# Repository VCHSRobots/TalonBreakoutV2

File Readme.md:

Talon Breakout Board, v2
------------------------

VCHS Robotics, Epic Robotz, Team 4415

December 2018

Epic Robotz has designed a breakout board that works with the Talon SRC manufactured by Cross
the Road Electronics.    This breakout board brings all signals from the data port to connectors
that provide secure connections for wiring to limit switches and encoders.  The breakout board
can be secured directly on the Talon, and the sensor/encoder wires can be directed inline with
the other Talon wiring to improve wire routing on the robot.  The connectors use a strong friction
fit to avoid becoming loose during a match.   This design of the breakout boards (and the
companion encoder PCB) was designed and tested during the Fall of 2018 by Epic Robotz
(Team 4415).  The design is being provided here for other teams to use if they see fit.
The boards where designed with a free version of Autodesk EAGLE pcb design software.  
All the files necessary to produce the breakout boards are included in this repository.

Notes
-----

The PCB is designed to be directly mounted in contact with the Talon.  Since the Talon is made of 
metal, care has been taken to place vias in areas where there is no metal on the Talon. However, 
when purchasing PCB boards with this design, be sure to put solder mask over the vias (which
is normally not done when fabricating prototypes).

It is also important to grind away any excess protrusion of through-hole pins on the solder side where
the connectors are soldered into place.  We have inclucded pictures to show how this is done.  Note
that the PCB traces to the connectors are ALL on the top side, so deep grinding of the bottom where
the connector pins protrude is okay.

For additional electrical insulation between the breakout board and the Talon, we suggest that you
epoxy a "gasket" direcly on the PCB.  All the files to 3D print the gasket are provided here as well
as pictures to show how the glue up is done.

We have included a design for a solder jig that holds the through-hole connectors in place while
soldering.  However, you will need to solder the SMD 2x5 connector with an oven or by hand
using a microscope and solder paste.

Bill of Materials
-----------------

    Talon PCB      --  Procured via a PCB manufacturing company using the gerber files.
                       Each PCB will produce 6 breakout boards, and 6 companion encoder boards.
    
    Gasket        --   1 Gasket per Breakout board.  Obtained via 3D printing.
    
    2x5 Connector --   1 per Breakout board.  Digikey 609-3706-1-ND.  This is an SMD part.
    
    4 pin Header  --   1 per Breakout board. Digikey WM16136-ND. This is a through hole part.
    
    3 pin Header  --   2 per Breakout board. Digikey WM2712-ND. This is a through hold part.
    
    Green LED     --   1 per companion encoder board. DigiKey 754-1131-1-ND. This is an SMD part.
    
    Blue LED      --   1 per companion encoder board. DigiKey 754-1437-1-ND. This is an SMD part.
    
    Red LED       --   1 per companion encoder board. DigiKey 754-1132-1-ND. This is an SMD part.
    
    1K Resistor   --   3 per companion encoder board. DigiKey 311-1.0KARCT-ND. This is an SMD part.

    5 Min Epoxy   --   A 3 oz 2-bottle kit will probably glue 100s of Gaskets.

To attach wires to the breakout board, you will need the following:

    3 Pos Housing   -- DigiKey WM2001-ND. One per limit switch

    4 Pos Housing   -- DigiKey WM2002-ND. One per encoder.
    
    Crimp Terminals -- DigiKey WM2312. 3 per limit switch, 4 per encoder.

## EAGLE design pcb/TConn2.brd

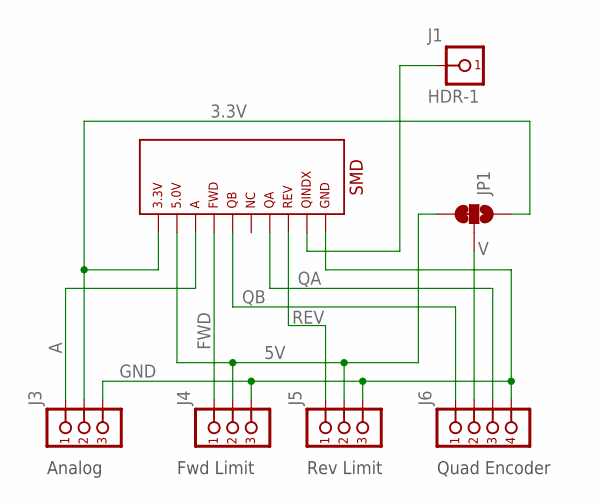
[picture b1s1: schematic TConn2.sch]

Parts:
J1: HDR-1; POST1X1
J3: HDR-3; POST1X3
J4, J5: HDR-3NYLON-RT-3; NYLON-RT-3
J6: HDR-4NYLON-RT-4; NYLON-RT-4
JP1: JUMPER-SMT_3_1-NC_TRACE_SILK; SMT-JUMPER_3_1-NC_TRACE_SILK
T1: TANON-HDR-THSMD-MOUNT; TALON-5X2-SMD2

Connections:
3.3V: J3.2, JP1.1, T1.P$1
5V: J4.P$2 (2), J5.P$2 (2), JP1.3, T1.P$2
A: J3.1, T1.P$3
FWD: J4.P$1 (1), T1.P$4
GND: J3.3, J4.P$3 (3), J5.P$3 (3), J6.P$4 (4), T1.P$10
unnamed: J1.1, T1.P$9
QA: J6.P$3 (3), T1.P$7
QB: J6.P$1 (1), T1.P$5
REV: J5.P$1 (1), T1.P$8
V: J6.P$2 (2), JP1.2

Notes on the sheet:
SMD
Quad Encoder
Rev Limit
Fwd Limit
Analog

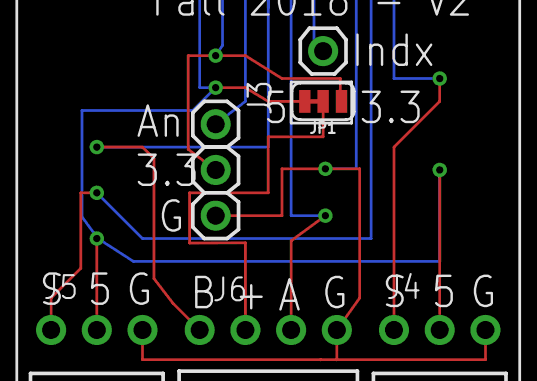
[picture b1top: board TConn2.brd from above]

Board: 2 copper layers, 7 parts (1 on the bottom side), 10 nets.

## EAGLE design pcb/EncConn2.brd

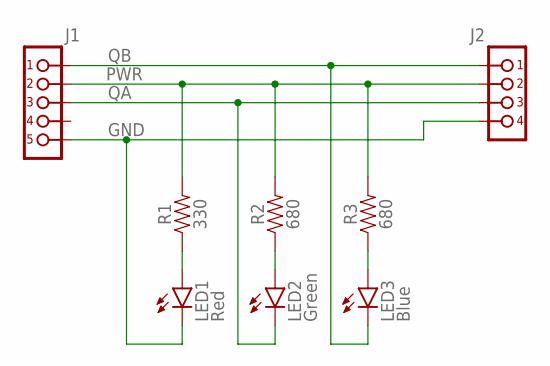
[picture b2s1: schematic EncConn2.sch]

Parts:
J1: HDR-5; POST1X5
J2: HDR-4NYLON-4; NYLON-4
LED1: Red; SML0805
LED2: Green; SML0805
LED3: Blue; SML0805
R1: 330; 0805
R2, R3: 680; 0805

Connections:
GND: J1.5, J2.P$4 (4), LED1.C
unnamed: LED1.A, R1.1
unnamed: LED3.A, R3.1
unnamed: LED2.A, R2.1
PWR: J1.2, J2.P$2 (2), R1.2, R2.2, R3.2
QA: J1.3, J2.P$3 (3), LED2.C
QB: J1.1, J2.P$1 (1), LED3.C

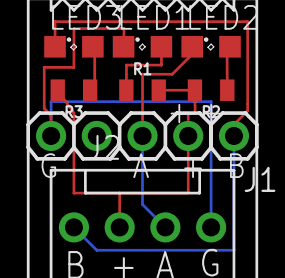
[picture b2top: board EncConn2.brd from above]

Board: 2 copper layers, 8 parts (0 on the bottom side), 7 nets.

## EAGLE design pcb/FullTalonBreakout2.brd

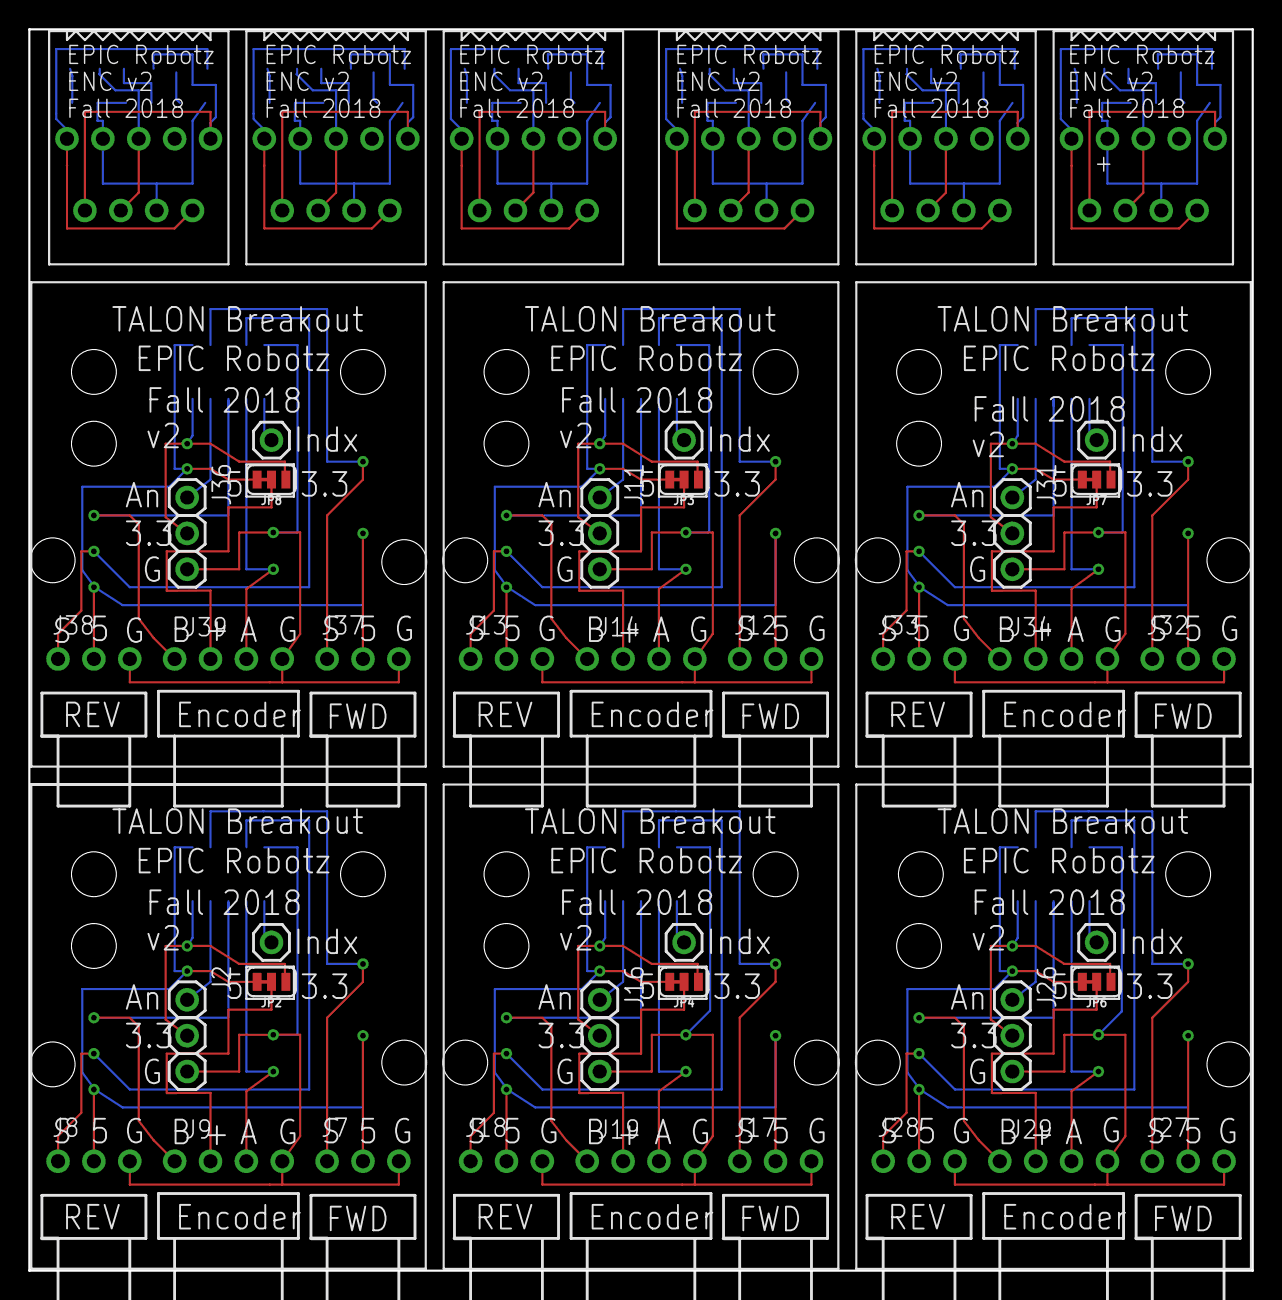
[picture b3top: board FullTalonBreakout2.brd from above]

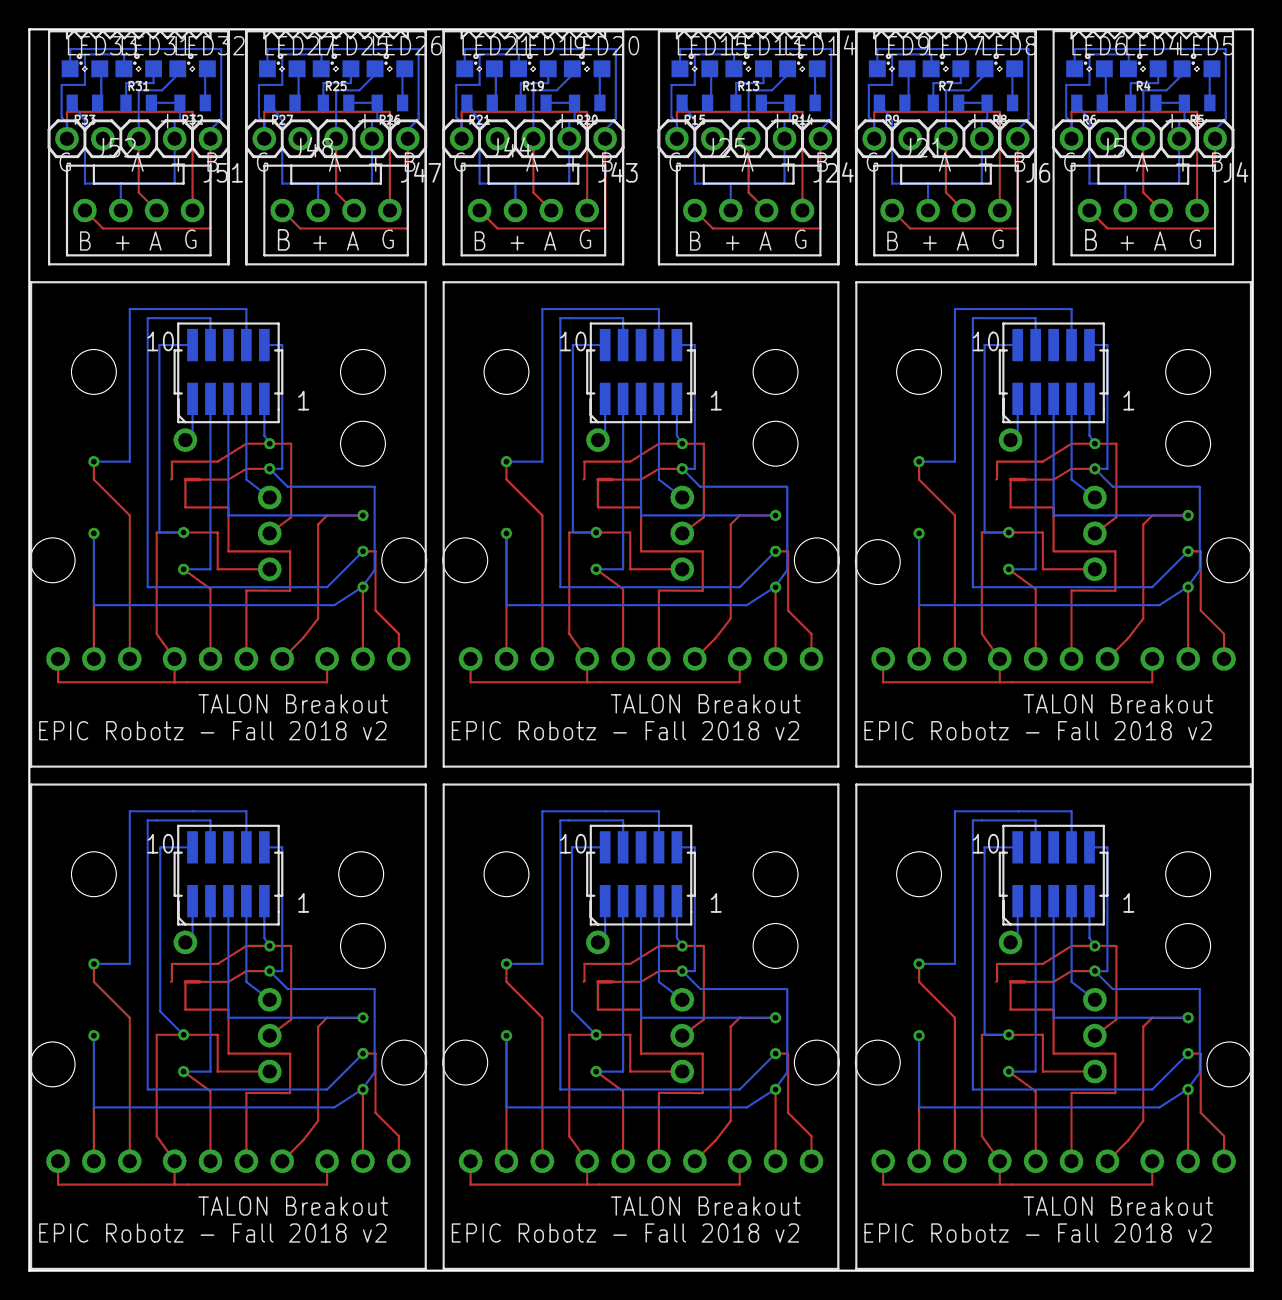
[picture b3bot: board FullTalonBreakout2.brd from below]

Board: 2 copper layers, 86.6 x 87.9 mm, 90 parts (54 on the bottom side), 102 nets.

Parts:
J2, J11, J16, J26, J31, J36: POST1X3
J4, J6, J24, J43, J47, J51: POST1X5
J5, J21, J25, J44, J48, J52: NYLON-4
J7, J8, J12, J13, J17, J18, J27, J28, J32, J33, J37, J38: NYLON-RT-3
J9, J14, J19, J29, J34, J39: HDR-4NYLON-RT-4; NYLON-RT-4
J10, J15, J20, J30, J35, J40: HDR-1; POST1X1
JP2, JP3, JP4, JP6, JP7, JP8: SMT-JUMPER_3_1-NC_TRACE_SILK
LED4, LED7, LED13, LED19, LED25, LED31: Red; SML0805
LED5, LED8, LED14, LED20, LED26, LED32: Green; SML0805
LED6, LED9, LED15, LED21, LED27, LED33: Blue; SML0805
R4, R7, R13, R19, R25, R31: 330; 0805
R5, R6, R8, R9, R14, R15, R20, R21, R26, R27, R32, R33: 680; 0805
T2, T3, T4, T6, T7, T8: TALON-5X2-SMD2

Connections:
3.3V: J16.2, JP4.1, T4.P$1
3.3V-1: J2.2, JP2.1, T2.P$1
3.3V-3: J26.2, JP6.1, T6.P$1
3.3V-4: J36.2, JP8.1, T8.P$1
3.3V-5: J11.2, JP3.1, T3.P$1
3.3V-6: J31.2, JP7.1, T7.P$1
5V-1: J7.P$2, J8.P$2, JP2.3, T2.P$2
5V-2: J17.P$2, J18.P$2, JP4.3, T4.P$2
5V-3: J27.P$2, J28.P$2, JP6.3, T6.P$2
5V-4: J37.P$2, J38.P$2, JP8.3, T8.P$2
5V-5: J12.P$2, J13.P$2, JP3.3, T3.P$2
5V-6: J32.P$2, J33.P$2, JP7.3, T7.P$2
A-1: J2.1, T2.P$3
A-2: J16.1, T4.P$3
A-3: J26.1, T6.P$3
A-4: J36.1, T8.P$3
A-5: J11.1, T3.P$3
A-6: J31.1, T7.P$3
FWD-1: J7.P$1, T2.P$4
FWD-2: J17.P$1, T4.P$4
FWD-3: J27.P$1, T6.P$4
FWD-4: J37.P$1, T8.P$4
FWD-5: J12.P$1, T3.P$4
FWD-6: J32.P$1, T7.P$4
GND-1: J2.3, J7.P$3, J8.P$3, J9.P$4, T2.P$10
GND-2: J16.3, J17.P$3, J18.P$3, J19.P$4, T4.P$10
GND-3: J26.3, J27.P$3, J28.P$3, J29.P$4, T6.P$10
GND-4: J36.3, J37.P$3, J38.P$3, J39.P$4, T8.P$10
GND-5: J11.3, J12.P$3, J13.P$3, J14.P$4, T3.P$10
GND-6: J31.3, J32.P$3, J33.P$3, J34.P$4, T7.P$10
GND-E1: J4.5, J5.P$4, LED4.C
GND-E2: J6.5, J21.P$4, LED7.C
GND-E3: J24.5, J25.P$4, LED13.C
GND-E4: J43.5, J44.P$4, LED19.C
GND-E5: J47.5, J48.P$4, LED25.C
GND-E6: J51.5, J52.P$4, LED31.C
unnamed: J10.1, T2.P$9
unnamed: J15.1, T3.P$9
unnamed: J20.1, T4.P$9
unnamed: J35.1, T7.P$9
unnamed: LED4.A, R4.1
unnamed: LED7.A, R7.1
unnamed: LED6.A, R6.1
unnamed: LED9.A, R9.1
unnamed: J30.1, T6.P$9
unnamed: LED5.A, R5.1
unnamed: LED8.A, R8.1
unnamed: J40.1, T8.P$9
unnamed: LED13.A, R13.1
unnamed: LED15.A, R15.1
unnamed: LED14.A, R14.1
unnamed: LED19.A, R19.1
unnamed: LED21.A, R21.1
unnamed: LED20.A, R20.1
unnamed: LED25.A, R25.1
unnamed: LED27.A, R27.1
unnamed: LED26.A, R26.1
unnamed: LED31.A, R31.1
unnamed: LED33.A, R33.1
unnamed: LED32.A, R32.1
PWR-E1: J4.2, J5.P$2, R4.2, R5.2, R6.2
PWR-E2: J6.2, J21.P$2, R7.2, R8.2, R9.2
PWR-E3: J24.2, J25.P$2, R13.2, R14.2, R15.2
PWR-E4: J43.2, J44.P$2, R19.2, R20.2, R21.2
PWR-E5: J47.2, J48.P$2, R25.2, R26.2, R27.2
PWR-E6: J51.2, J52.P$2, R31.2, R32.2, R33.2
QA-1: J9.P$3, T2.P$7
QA-2: J19.P$3, T4.P$7
QA-3: J29.P$3, T6.P$7
QA-4: J39.P$3, T8.P$7
QA-5: J14.P$3, T3.P$7
QA-6: J34.P$3, T7.P$7
QA-E1: J4.3, J5.P$3, LED5.C
QA-E2: J6.3, J21.P$3, LED8.C
QA-E3: J24.3, J25.P$3, LED14.C
QA-E4: J43.3, J44.P$3, LED20.C
QA-E5: J47.3, J48.P$3, LED26.C
QA-E6: J51.3, J52.P$3, LED32.C
QB-1: J9.P$1, T2.P$5
QB-2: J19.P$1, T4.P$5
QB-3: J29.P$1, T6.P$5
QB-4: J39.P$1, T8.P$5
QB-5: J14.P$1, T3.P$5
QB-6: J34.P$1, T7.P$5
QB-E1: J4.1, J5.P$1, LED6.C
QB-E2: J6.1, J21.P$1, LED9.C
QB-E3: J24.1, J25.P$1, LED15.C
QB-E4: J43.1, J44.P$1, LED21.C
QB-E5: J47.1, J48.P$1, LED27.C
QB-E6: J51.1, J52.P$1, LED33.C
REV-1: J8.P$1, T2.P$8
REV-2: J18.P$1, T4.P$8
REV-3: J28.P$1, T6.P$8
REV-4: J38.P$1, T8.P$8
REV-5: J13.P$1, T3.P$8
REV-6: J33.P$1, T7.P$8
V-1: J9.P$2, JP2.2
V-2: J19.P$2, JP4.2
V-3: J29.P$2, JP6.2
V-4: J39.P$2, JP8.2
V-5: J14.P$2, JP3.2
V-6: J34.P$2, JP7.2

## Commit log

2018-12-23 Final Design for V2
2018-12-23 fixing doc
2019-01-04 Fixed our name!
2019-01-04 More Name Fixes

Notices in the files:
parts and their libraries:
SparkFun-Resistors: Licensing: Creative Commons ShareAlike 4.0 International - https://creativecommons.org/licenses/by-sa/4.0
